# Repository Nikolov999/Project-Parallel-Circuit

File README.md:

# Project-Parallel-Circuit

A first hands-on KiCad PCB project built to explore a real parallel DC circuit from electrical calculation through schematic capture, footprint assignment, PCB layout, routing, verification, and 3D inspection.

The board uses a 5 V input and two independent LED branches. Each branch contains its own 330 Ω current-limiting resistor and LED, so the resistor/LED pair is series-connected inside the branch while the two complete branches are connected in parallel.

## Circuit architecture

```text
                     Branch 1
              R1 330 Ω        D1
          +---/\/\/\/---------|>|---+
          |                         |
+5 V -----+                         +----- GND
          |                         |
          +---/\/\/\/---------|>|---+
              R2 330 Ω        D2
                     Branch 2
```

Electrical structure:

- J1 pin 1: +5 V input
- J1 pin 2: GND
- Branch 1: +5 V -> R1 -> D1 -> GND
- Branch 2: +5 V -> R2 -> D2 -> GND
- R1 and D1 are in series.
- R2 and D2 are in series.
- The two branches are in parallel.

## Electrical calculations

Design assumptions:

- Supply voltage, `Vs` = 5 V
- Approximate LED forward voltage, `Vf` = 2 V
- Current-limiting resistance per branch = 330 Ω

Voltage across each resistor:

```text
Vr = Vs - Vf
Vr = 5 V - 2 V
Vr = 3 V
```

Approximate branch current:

```text
I = Vr / R
I = 3 V / 330 Ω
I ≈ 0.00909 A
I ≈ 9.1 mA
```

Because the branches are parallel and use the same nominal component values:

```text
I1 ≈ 9.1 mA
I2 ≈ 9.1 mA
Itotal = I1 + I2
Itotal ≈ 18.2 mA
```

Approximate resistor dissipation:

```text
P = Vr × I
P ≈ 3 V × 0.00909 A
P ≈ 0.027 W
```

A 0.25 W resistor rating therefore provides substantial margin for the assumed operating point.

> `Vf = 2 V` is a design approximation. Real LED forward voltage varies with LED type, colour, current, temperature, and manufacturing tolerance, so measured current will differ somewhat from the calculated value.

## Schematic

The schematic was built with two independent current-limited LED branches tied between the same +5 V and GND nodes. Power flags are used so KiCad's electrical rules checker understands that the rails are driven from an external source through J1.

## PCB layout

The board is intentionally spacious so the two branches are visually obvious. The current revision uses:

- Board outline: 102 mm × 42 mm
- Board thickness setting: 1.6 mm
- Routing layer: F.Cu
- Track width: 0.20 mm
- Vias: none
- Through-hole components throughout

## 3D views

## Components

| Reference | Qty | Value / Part | Footprint |
|---|---:|---|---|
| J1 | 1 | 1×02 connector | `PinHeader_1x02_P2.54mm_Vertical` |
| R1, R2 | 2 | 330 Ω resistor | `R_Axial_DIN0207_L6.3mm_D2.5mm_P2.54mm_Vertical` |
| D1, D2 | 2 | 5 mm LED | `LED_D5.0mm` |

A machine-readable version is available in [`BOM.csv`](BOM.csv).

## Design verification

Final checks completed in KiCad:

- Electrical Rules Checker reviewed
- Design Rules Checker reviewed
- Unconnected items cleared
- PCB / schematic parity checked
- LED polarity corrected and verified
- 3D board inspection completed

## Repository structure

```text
Project-Parallel-Circuit/
├── README.md
├── BOM.csv
├── .gitignore
├── .gitattributes
├── kicad/
│   ├── Project-Parallel-Circuit.kicad_pro
│   ├── Project-Parallel-Circuit.kicad_sch
│   └── Project-Parallel-Circuit.kicad_pcb
├── docs/
│   ├── board-definition.md
│   ├── calculations.md
│   ├── design-notes.md
│   └── source-notes/
│       ├── Board-Definition-original.txt
│       └── Calculating-Branches-original.txt
├── images/
│   ├── schematic.png
│   ├── pcb-layout.png
│   ├── pcb-3d-front.png
│   └── pcb-3d-angle.png
└── fabrication/
    ├── README.md
    ├── Project-Parallel-Circuit-Gerbers.zip
    ├── gerbers/
    │   ├── Project-Parallel-Circuit-F_Cu.gbr
    │   ├── Project-Parallel-Circuit-B_Cu.gbr
    │   ├── Project-Parallel-Circuit-F_Mask.gbr
    │   ├── Project-Parallel-Circuit-B_Mask.gbr
    │   ├── Project-Parallel-Circuit-F_Silkscreen.gbr
    │   ├── Project-Parallel-Circuit-B_Silkscreen.gbr
    │   ├── Project-Parallel-Circuit-Edge_Cuts.gbr
    │   └── Project-Parallel-Circuit-job.gbrjob
    └── drill/
        ├── Project-Parallel-Circuit-PTH.drl
        └── Project-Parallel-Circuit-NPTH.drl
```

## What this project demonstrates

- Ohm's law
- Kirchhoff's Current Law
- Kirchhoff's Voltage Law
- Series elements inside parallel branches
- Independent LED current limiting
- LED polarity and anode/cathode mapping
- KiCad schematic capture
- ERC workflow
- Footprint assignment
- PCB placement and routing
- Board outlines with `Edge.Cuts`
- Silkscreen labeling
- DRC and schematic/PCB parity checks
- 3D mechanical inspection

## Software

Designed with KiCad 10.

## Fabrication outputs

The repository includes the final Gerber job, separate manufacturing layers, plated/non-plated Excellon drill files, and a ready-to-upload manufacturing ZIP. The corrected export keeps `Plot on All Layers` empty so copper and silkscreen are not duplicated into unrelated manufacturing layers.

Basic checks performed on this export:

- `Edge_Cuts` contains only the closed 102 mm × 42 mm board profile.
- `F.Cu` contains the front routing and through-hole pads.
- `B.Cu` contains through-hole pad copper without copied front routing.
- `Project-Parallel-Circuit-PTH.drl` contains 10 plated component holes.
- `Project-Parallel-Circuit-NPTH.drl` is empty because the board has no NPTH mechanical holes.

See [`fabrication/README.md`](fabrication/README.md) for the file set.

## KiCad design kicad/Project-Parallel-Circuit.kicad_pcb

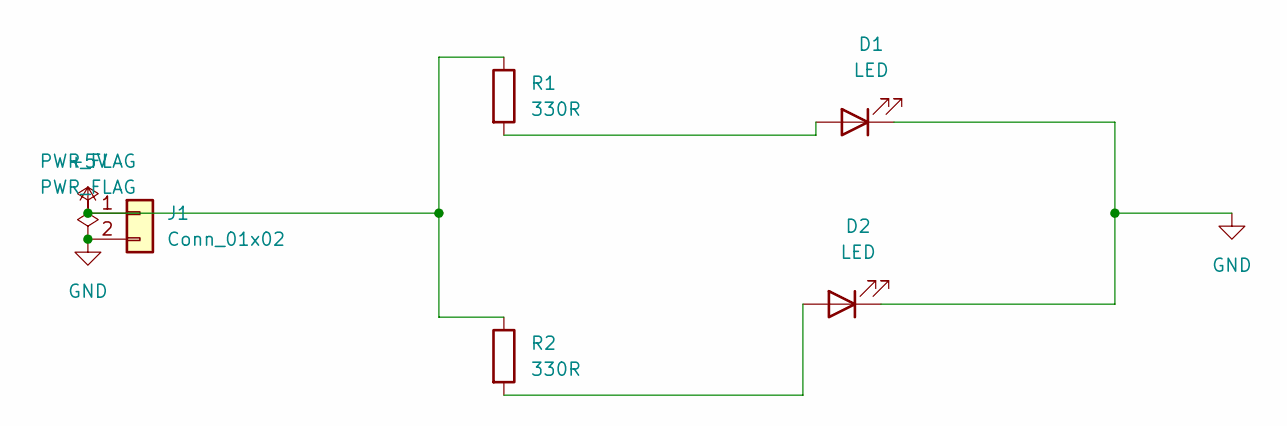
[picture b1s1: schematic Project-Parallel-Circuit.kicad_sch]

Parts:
D1, D2: LED; LED_D5.0mm
J1: Conn_01x02; PinHeader_1x02_P2.54mm_Vertical
R1, R2: 330R; R_Axial_DIN0207_L6.3mm_D2.5mm_P2.54mm_Vertical

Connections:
+5V: J1.1, R1.1, R2.1
GND: D1.1 (K), D2.1 (K), J1.2
unnamed: D1.2 (A), R1.2
unnamed: D2.2 (A), R2.2

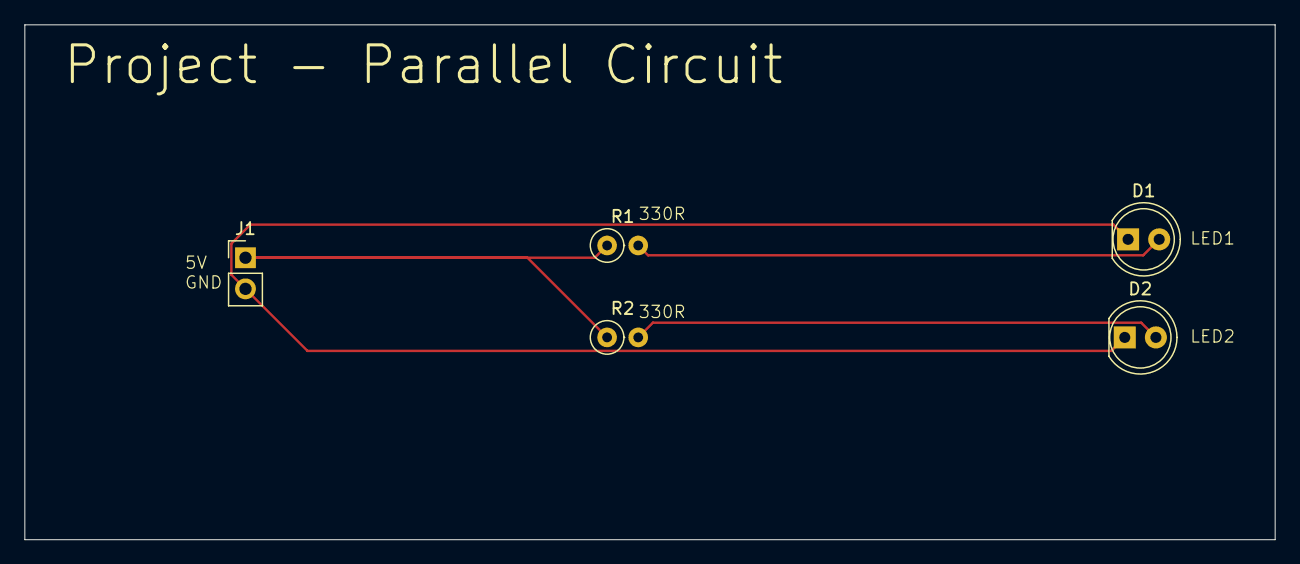
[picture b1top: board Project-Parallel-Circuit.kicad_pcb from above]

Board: 2 copper layers, 102.0 x 42.0 mm, 5 parts (0 on the bottom side), 4 nets.
